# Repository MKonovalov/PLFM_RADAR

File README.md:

# AERIS-10: Open Source Pulse Linear Frequency Modulated Phased Array Radar

AERIS-10 is an open-source, low-cost 10.5 GHz phased array radar system featuring Pulse Linear Frequency Modulated (LFM) modulation. Available in two versions (3km and 20km range, see [Basis of the published performance numbers](#-basis-of-the-published-performance-numbers) for the detection assumptions behind the range figures), it's designed for researchers, drone developers, and serious SDR enthusiasts who want to explore and experiment with phased array radar technology.

## 📡 Overview

The AERIS-10 project aims to democratize radar technology by providing a fully open-source, modular, and hackable radar system. Whether you're a university researcher, a drone startup, or an advanced maker, AERIS-10 offers a platform for experimenting with beamforming, pulse compression, Doppler processing, and target tracking.

## 🔬 Key Features

- **Open Source Hardware & Software** - Complete schematics, PCB layouts, firmware, and software available
- **Dual Version Availability**:
  - **AERIS-10N (Nexus)**: 3km range with 8x16 patch antenna array
  - **AERIS-10E (Extended)**: 20km range with 32x16 dielectric-filled slotted waveguide array
- **Full Electronic Beam Steering** - ±45° electronic steering in elevation and azimuth (characterised for the 8x16 patch array in `docs/AERIS_Antenna_Report.pdf`; the 32x16 waveguide array has no published element-pattern analysis yet — see the basis section below)
- **Advanced Signal Processing** - On-board FPGA handles pulse compression, Doppler FFT, MTI, and CFAR
- **Python GUI** - User-friendly interface with map integration
- **GPS/IMU Integration** - Real-time position and attitude correction
- **Modular Design** - Separate power management, frequency synthesis, and RF boards

## 🏗️ System Architecture

### Hardware Components

The AERIS-10 main sub-systems are:

- **Power Management Board** - Supplies all necessary voltage levels to the electronics components with proper filtering and sequencing (sequencing ensured by the microcontroller)

- **Frequency Synthesizer Board** - Uses a high-performance Low Jitter Clock Generator (AD9523-1) that supplies phase-aligned clock references for:
  - RX and TX Frequency Synthesizers (ADF4382)
  - DAC
  - ADC
  - FPGA

- **Main Board** containing:
  - **DAC** - Generates the RADAR Chirps
  - **2x Microwave Mixers (LTC5552)** - For up-conversion and IF-down-conversion
  - **4x 4-Channel Phase Shifters (ADAR1000)** - For RX and TX chain beamforming
  - **16x Front End Chips (ADTR1107)** - Used for both Low Noise Amplifying (RX) and Power Amplifying (TX) stages
  - **XC7A50T FPGA** - Handles RADAR Signal Processing on the upstream FTG256 board:
    - PLFM Chirps generation via the DAC
    - Raw ADC data read
    - Hybrid Automatic Gain Control (AGC) — cross-layer FPGA/STM32/GUI loop
    - I/Q Baseband Down-Conversion
    - Decimation
    - Filtering
    - Forward FFT
    - Pulse Compression
    - Doppler, MTI and CFAR processing
    - USB Interface
  - **STM32F746xx Microcontroller** - Used for:
    - Power-up and power-down sequencing (see Power Management Excel File)
    - FPGA communication
    - Setup and Interface with:
      - Clock Generator (AD9523-1)
      - 2x Frequency Synthesizers (ADF4382)
      - 4x 4-Channel Phase Shifters (ADAR1000) for RADAR pulse sequencing
      - 2x ADS7830 8-channel I²C ADCs (Main Board, U88 @ 0x48 / U89 @ 0x4A) for 16x Idq measurement, one per PA channel, each sensed through a 5 mΩ shunt on the PA board and an INA241A3 current-sense amplifier (x50) on the Main Board
      - 2x DAC5578 8-channel I²C DACs (Main Board, U7 @ 0x48 / U69 @ 0x49) for 16x Vg control, one per PA channel; closed-loop calibrated at boot to the target Idq
      - GPS module (UM982) for GUI map centering and per-detection position tagging
      - GY-85 IMU for pitch/roll correction of target coordinates
      - BMP180 Barometer
      - Stepper Motor
      - 1x ADS7830 8-channel I²C ADC (Main Board, U10) reading 8 thermistors for thermal monitoring; a single GPIO (EN_DIS_COOLING) switches the cooling fans on when any channel exceeds the threshold
      - RF switches

- **16x Power Amplifier Boards** - Used only for AERIS-10E version, featuring 10Watt QPA2962 GaN amplifier for extended range

- **Antenna Arrays**:
  - **AERIS-10N (Nexus)** - 8x16 patch antenna array
  - **AERIS-10X (Extended)** - 32x16 dielectric-filled slotted waveguide antenna array

- **Miscellaneous Components**:
  - Slip-Ring
  - Stepper Motor and drivers
  - Cooling Fans
  - Enclosure

### Processing Pipeline

1. **Waveform Generation** - DAC creates LFM chirps
2. **Up/Down Conversion** - LTC5552 mixers handle frequency translation
3. **Beam Steering** - ADAR1000 phase shifters control 16 elements
4. **Signal Processing (FPGA)**:
   - Raw ADC data capture
   - I/Q baseband down-conversion
   - Decimation & filtering (CIC/FIR)
   - Pulse compression
   - Doppler FFT processing
   - MTI & CFAR detection
5. **System Management (STM32)**:
   - Power sequencing
   - Peripheral configuration
   - GPS/IMU integration
   - Stepper motor control
6. **Visualization (Python GUI)**:
   - Real-time target plotting
   - Map integration
   - Radar control interface

<!-- V6 GIF removed — V6 is deprecated. V65 Tk and V7 PyQt6 are the active GUIs. -->

## 📊 Technical Specifications

| Parameter | AERIS-10N (Nexus) | AERIS-10X (Extended) |
|-----------|-------------------|----------------------|
| **Frequency** | 10.5 GHz | 10.5 GHz |
| **Max Range** | 3 km ¹ | 20 km ¹ |
| **Antenna** | 8x16 Patch Array | 32x16 Slotted Waveguide |
| **Beam Steering** | Electronic (±45°) ² | Electronic (±45°) ² |
| **Mechanical Scan** | 360° (stepper motor) | 360° (stepper motor) |
| **Output Power** | ~1W×16 | 10W×16 (GaN amplifier) |
| **Processing** | FPGA + STM32 | FPGA + STM32 |
| **Data Interface** | FT2232H USB 2.0 — ~40 MB/s ³ | FT2232H USB 2.0 — ~40 MB/s ³ |

## 📐 Basis of the published performance numbers

The figures above are specifications the design targets, not measured results from a
built unit.  They are only meaningful with their detection assumptions attached, so:

1. **Range.** The 3 km / 20 km figures are single-pulse-budget numbers for a **1 m² RCS**
   target at long dwell (many pulses integrated coherently).  Detection range scales as the
   fourth root of RCS and as the fourth root of integration time, so the same radar sees a
   **0.01 m² target (small drone) at roughly 6 km**, not 20 km.  Quote the target RCS and
   the dwell whenever you quote a range.  The repository carries no link-budget document
   that derives these numbers; `docs/AERIS_Antenna_Report.pdf` covers antenna gain and
   element pattern only.
2. **Beam steering.** ±45° with ~2–3 dB scan loss is the characterised result for the
   **8x16 patch array** (4.72 dBi element, 21.1 dB array factor, ~25.8 dBi realised gain,
   ~75–85° element half-power beamwidth).  Applying the same figure to the 32x16
   slotted-waveguide array is an extrapolation: no element pattern, grating-lobe analysis
   or measured scan loss is published for that array yet.
3. **Data interface.** The FT2232H interface runs at 60 MHz (≈40 MB/s), while the
   400 MSPS ADC produces ≈3.2 Gbit/s raw.  The link therefore carries **processed
   detections/Doppler products only — there is no raw IQ streaming path** at full rate.
4. **The waveguide array's dimensions do not agree inside its own spec.**
   `Dielectric_Filled_Waveguide_Array_Spec.docx` states an inter-column pitch of
   λ₀/2 ≈ 14.28 mm and a **panel height (16 columns) of 223 mm**.  Sixteen columns at
   that pitch span 16 × 14.28 = **228.5 mm**, and the centre-to-centre aperture is
   15 × 14.28 = **214.2 mm** — so 223 mm matches neither convention (5.5 mm and 8.8 mm
   apart respectively).  The spec's own directivity (27.73 dBi) and EIRP (54.8 dBW) are
   derived from A = 0.173 m × 0.223 m = 0.0385 m², i.e. they use the 223 mm height.
   The fabrication drawing has to say which convention it uses before a panel is cut:
   the directivity difference is only ~0.2 dB, so the performance number stands either
   way — it is the drawing that needs reconciling with the spec table.

   **Harmonic emissions.**  Wherever EIRP is quoted above, the harmonic figure belongs with it: the
   PA's 2nd and 3rd harmonics (21.0 and 31.5 GHz) are suppressed by the inline output filter, whose
   specification is in `docs/harmonic-filter.md`.  The chosen part rejects **≥40 dB across
   19.5–32 GHz**, against a requirement of ≥20 dB below carrier at the antenna port — so the design
   carries 20 dB of margin, and the *measured* figure is a first-article item recorded in
   `docs/bring-up-acceptance.md`.

## 🚀 Getting Started

### 🧹 Repository File Placement Policy

To keep the repository root clean and make artifacts easy to find, place generated files in the following locations:

- **Published reports (tracked, GitHub Pages):** `docs/`
  - Example: `docs/AERIS_Simulation_Report_v2.pdf`
- **Simulation-generated outputs (local, gitignored):** `5_Simulations/generated/`
  - Plots, scenario outputs, temporary analysis directories
- **FPGA/Vivado generated artifacts (local, gitignored):** `9_Firmware/9_2_FPGA/reports/`
  - VCD/VVP dumps, temporary CSVs, local report snapshots
- **Reusable FPGA automation scripts (tracked):** `9_Firmware/9_2_FPGA/scripts/`
  - TCL flows, helper scripts used by build/bring-up
- **Generated board artifacts (tracked):** `4_Schematics and Boards Layout/4_7_Production Files/Board_Artifacts/`
  - BOM/CPL CSVs, the DNP list, the inter-board rail map and the accepted-discrepancy baseline,
    all regenerated by `9_Firmware/tools/` and checked in CI

**Do not leave generated artifacts in the repository root.**

### Prerequisites

- Basic understanding of radar principles
- Experience with PCB assembly (for hardware build)
- Python 3.8+ for the GUI software
- FPGA development tools (Vivado) for signal processing modifications

### Hardware Assembly

1. **Order PCBs**: Production outputs are under `/4_Schematics and Boards Layout/4_7_Production Files`
2. **Source Components**: BOM/CPL files are co-located under `/4_Schematics and Boards Layout/4_7_Production Files`
3. **Assembly**: Use the schematics in `/4_Schematics and Boards Layout/4_6_Schematics` together with the production outputs above; a standalone assembly guide is not currently tracked
4. **Antenna**: Choose appropriate array files for your target variant
5. **Enclosure**: Mechanical drawings currently live in `/8_Utils/Mechanical_Drawings`

## 📜 License

This project is open-source but uses **different licenses for hardware and software** to ensure proper legal coverage.

### Hardware Documentation
The hardware design files—including:
- Schematics and PCB layouts (in `/4_Schematics and Boards Layout`)
- Bill of Materials (BOM) files
- Gerber files and manufacturing outputs
- Mechanical drawings and enclosure designs

are licensed under the **CERN Open Hardware Licence Version 2 – Permissive (CERN-OHL-P)** .

This is a hardware-specific license that:
- ✅ Clearly defines "Hardware," "Documentation," and "Products"
- ✅ Includes explicit patent protection for contributors and users
- ✅ Provides stronger liability limitations (important for high-power RF)
- ✅ Aligns with professional open-hardware standards (CERN, OSHWA)

You may use, modify, and sell products based on these designs, provided you:
- Maintain the original copyright notices
- Distribute any modified designs under the same license
- Make your modifications available in Source format

### Software and Firmware
The software components—including:
- FPGA code (VHDL/Verilog in `/9_Firmware`)
- Microcontroller firmware (STM32)
- Python GUI and utilities

remain under the **MIT License** for maximum flexibility.

### Full License Texts
- The complete CERN-OHL-P license text is in the `Licence` file (note the spelling — there is no `LICENSE` file)
- The MIT text covering `9_Firmware` (MCU firmware, FPGA RTL, tools) and the GUI/SDK is in `9_Firmware/LICENSE`

### Why This Change?
Originally, the entire project used the MIT license. The community (special thanks to gmaynez!) pointed out that MIT lacks legal protections needed for physical hardware. The switch to CERN-OHL-P ensures the project is properly protected while maintaining the same permissive spirit.

## 📚 Documentation

Comprehensive documentation is available in the `/docs` folder and served via GitHub Pages at [https://NawfalMotii79.github.io/PLFM_RADAR/docs/](https://NawfalMotii79.github.io/PLFM_RADAR/docs/):

- [System Architecture](/docs/architecture.html)
- [Implementation Log](/docs/implementation-log.html)
- [Hardware Bring-Up Guide](/docs/bring-up.html)
- [Test Reports](/docs/reports.html)
- [Release Notes](/docs/release-notes.html)

### 🔧 Regenerating the BOM and CPL

The production BOM/CPL for each board is generated from the Eagle board files rather than
transcribed by hand, so it can be checked instead of trusted:

```bash
python3 9_Firmware/tools/regenerate_bom.py . --check
```

`--check` exits non-zero when a placed part is missing from a committed BOM spreadsheet,
when a sheet lists a designator that is not on the board, or when a placed part has no
orderable value/MPN.  Run it before ordering boards.

## 🤝 Contributing

We welcome contributions! Please see our [Contributing Guidelines](/CONTRIBUTING.md) for details on repo layout, branch workflow, and basic PR checks.

Areas where help is especially appreciated:
- **RF Engineers**: Review designs, optimize antenna performance
- **FPGA Developers**: Optimize signal processing pipeline
- **Software Developers**: Enhance Python GUI and SDK
- **Beta Testers**: University researchers, drone startups, advanced makers

## 📞 Contact & Collaboration

I welcome serious inquiries from researchers, engineers, and potential collaborators. However, due to the high volume of interest in this project, please understand that I cannot guarantee a response to every message.

- **Technical questions or bug reports**: Please [open a GitHub issue](https://github.com/NawfalMotii79/PLFM_RADAR/issues) so the whole community can benefit from the discussion.
- **Collaboration, licensing, or business inquiries**: 📧 nawfal.motii.33 [at] gmail [dot] com

## 💰 Sponsors

---

**Star ⭐ this repository if you're interested in open-source radar technology!**

*Note: This is an active development project. Some features are still in progress. Check the issues page for known limitations and upcoming features.*

## 19,000 stars – Thank you

This project started in a small workshop in Morocco. Today, 19,000 engineers on GitHub have starred it.

I am genuinely humbled.

**What this tells me:**

- Open source radar matters
- Affordable sensing is needed
- Engineers want to build, not just buy

Thank you to everyone who starred, forked, opened issues, submitted PRs, and shared this project.

The work continues.

**Nawfal Motii**
ABAC INDUSTRY
(http://www.abacindustry.com)

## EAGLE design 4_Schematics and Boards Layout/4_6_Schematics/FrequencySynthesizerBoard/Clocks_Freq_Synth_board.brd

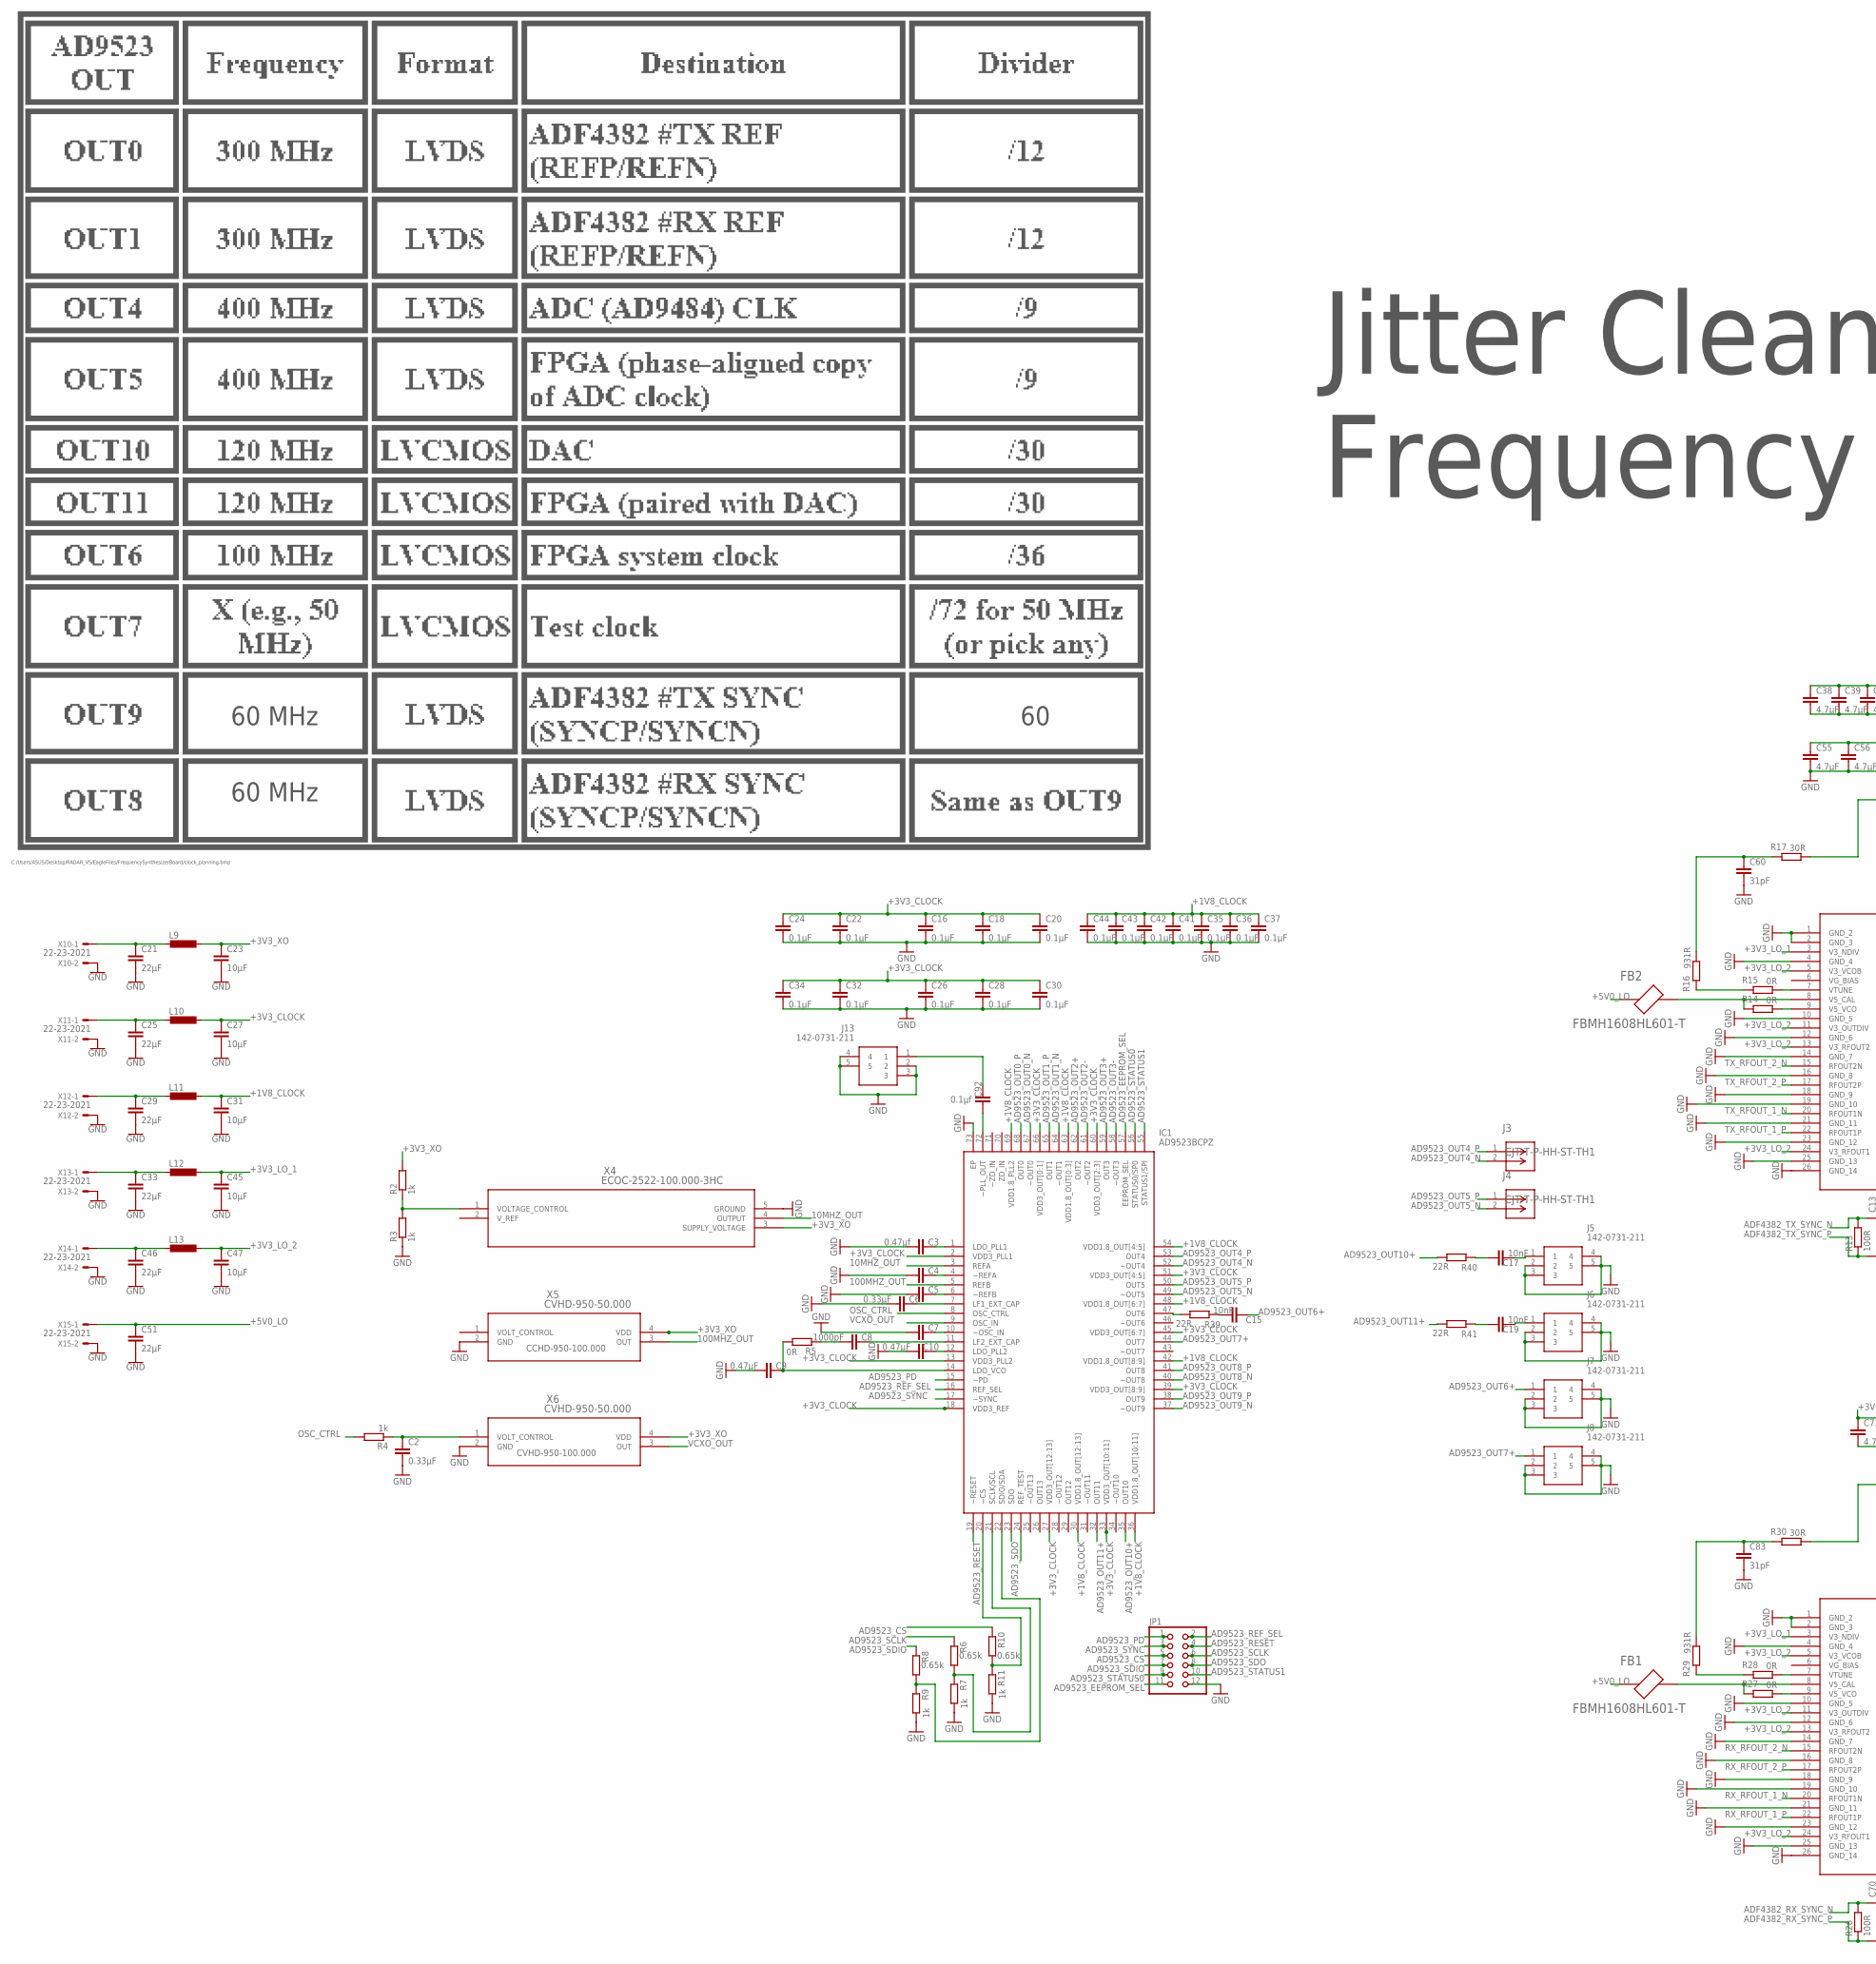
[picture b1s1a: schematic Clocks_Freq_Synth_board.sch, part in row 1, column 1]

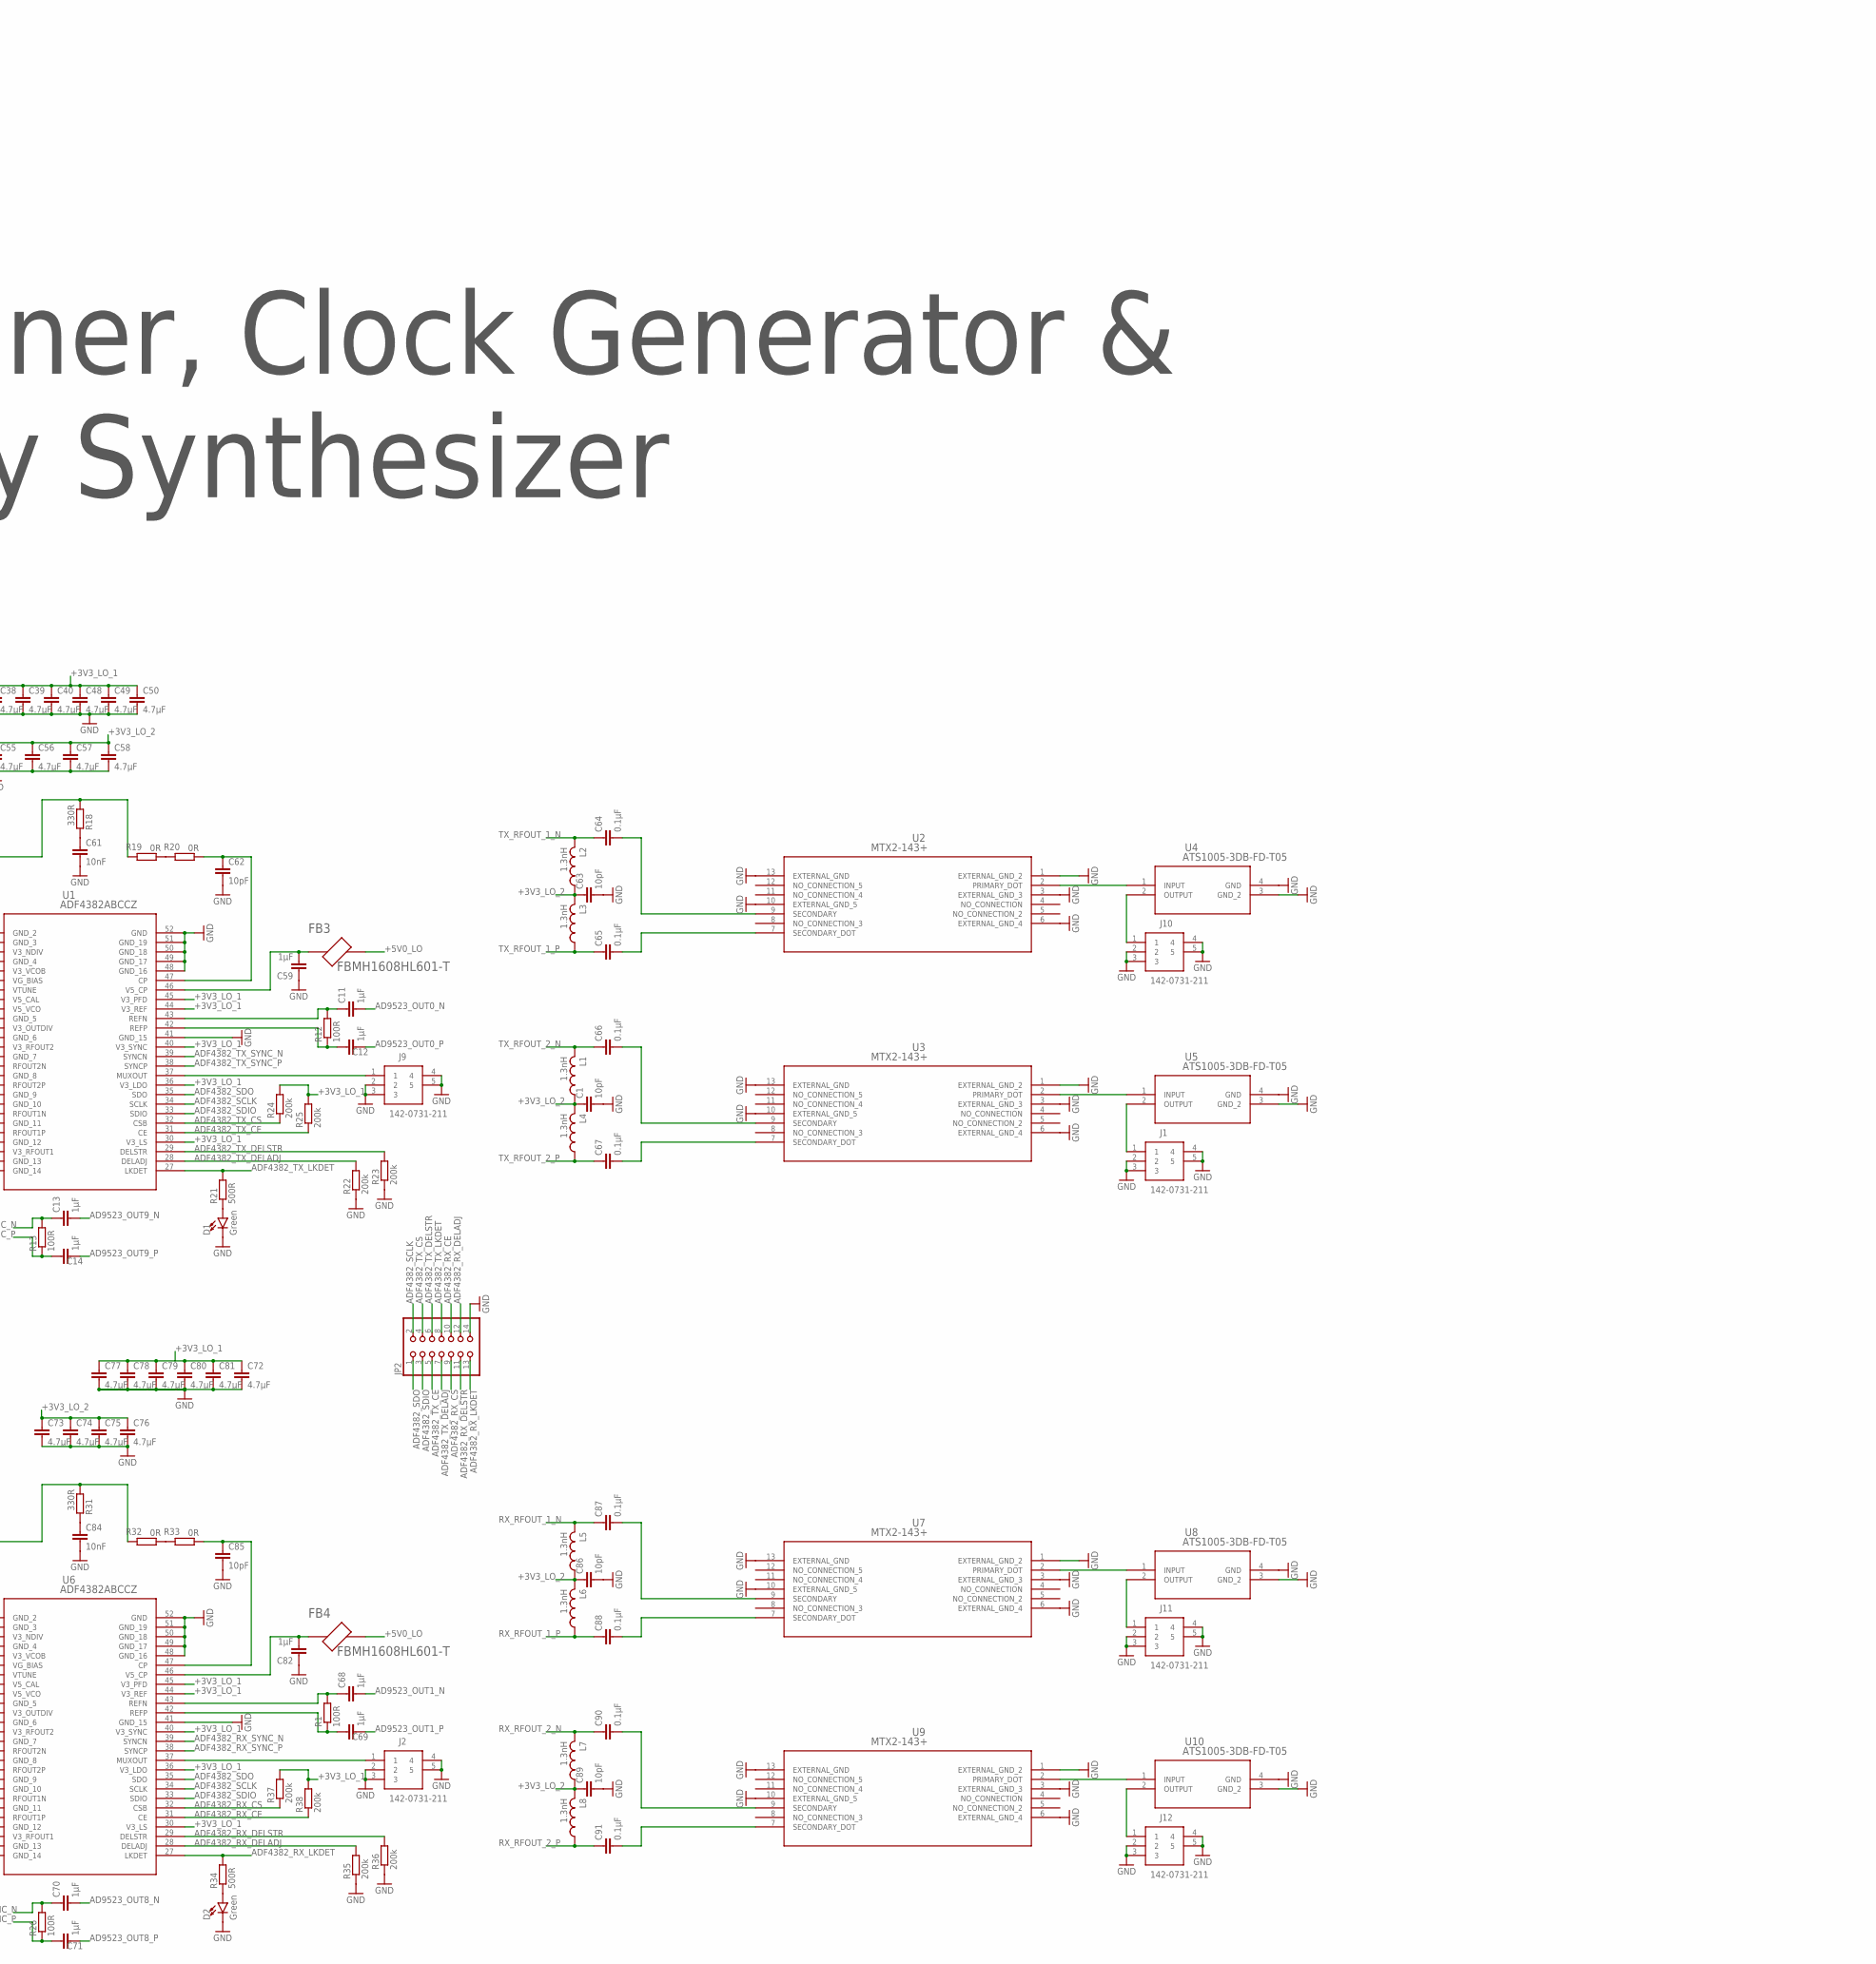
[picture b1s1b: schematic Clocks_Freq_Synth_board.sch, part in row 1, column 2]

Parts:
C1, C62, C63, C85, C86, C89: 10pF; C0201
C2, C6: 0.33µF; C0201
C3: 0.47µf; C0201
C4, C5, C7: C-EUC0201; C0201
C8: 1000pF; C0201
C9, C10: 0.47µF; C0201
C11, C12, C13, C14, C59, C68, C69, C70, C71, C82: 1µF; C0201
C15, C17, C19: 10nF; C0402
C16, C18, C20, C22, C24, C26, C28, C30, C32, C34, C35, C36, C37, C41, C42, C43, C44, C64, C65, C66, C67, C87, C88, C90, C91: 0.1µF; C0201
C21, C25, C29, C33, C46, C51: 22µF; C1210
C23, C27, C31, C45, C47: 10µF; C1210
C38, C39, C40, C48, C49, C50, C55, C56, C57, C58, C72, C73, C74, C75, C76, C77, C78, C79, C80, C81: 4.7µF; C0201
C60, C83: 31pF; C0201
C61, C84: 10nF; C0201
C92: 0.1µf; C0201
D1, D2: Green; LED-0603
FB1, FB2, FB3, FB4: FBMH1608HL601-T; BEADC1608X90N
IC1: AD9523BCPZ; QFN50P1000X1000X100-73N
J1, J2, J5, J6, J7, J8, J9, J10, J11, J12, J13: 142-0731-211; 1420731211
J3, J4: CJT-T-P-HH-ST-TH1; CONN_CJT-T-P-XX-ST-TH1_SAI
JP1: PINHD-2X6; 2X06
JP2: PINHD-2X7; 2X07
L1, L2, L3, L4, L5, L6, L7, L8: 1.3nH; L0201
L9, L10, L11, L12, L13: L-EUL5650M; L5650M
R1, R12, R13, R26: 100R; R0201
R2, R3, R4, R7, R9, R11: 1k; R0201
R5, R14, R15, R19, R20, R27, R28, R32, R33: 0R; R0201
R6, R8, R10: 0.65k; R0201
R16, R29: 931R; R0201
R17, R30: 30R; R0201
R18, R31: 330R; R0201
R21, R34: 500R; R0201
R22, R23, R24, R25, R35, R36, R37, R38: 200k; R0201
R39, R40, R41: 22R; R0201
U1, U6: ADF4382ABCCZ; CC-48-10_ADI
U2, U3, U7, U9: MTX2-143+; DQ1225_MNC
U4, U5, U8, U10: ATS1005-3DB-FD-T05; SMT_DB-FD-T05_SUS
X4: ECOC-2522-100.000-3HC; SMD5_ECOC-2522_25P4X22_ECS
X5, X6: CVHD-950-50.000; SMD4_CVHD-950_CRX
X10, X11, X12, X13, X14, X15: 22-23-2021

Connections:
10MHZ_OUT: IC1.3 (REFA), X4.4 (OUTPUT)
100MHZ_OUT: IC1.5 (REFB), X5.3 (OUT)
+1V8_CLOCK: C31.1, C35.1, C36.1, C37.1, C41.1, C42.1, C43.1, C44.1, IC1.30 (VDD1.8_OUT[12:13]), IC1.36 (VDD1.8_OUT[10:11]), IC1.42 (VDD1.8_OUT[8:9]), IC1.48 (VDD1.8_OUT[6:7]), IC1.54 (VDD1.8_OUT[4:5]), IC1.63 (VDD1.8_OUT[0:3]), IC1.69 (VDD1.8_PLL2), L11.1
+3V3_CLOCK: C16.1, C18.1, C20.1, C22.1, C24.1, C26.1, C27.1, C28.1, C30.1, C32.1, C34.1, IC1.2 (VDD3_PLL1), IC1.13 (VDD3_PLL2), IC1.18 (VDD3_REF), IC1.27 (VDD3_OUT[12:13]), IC1.33 (VDD3_OUT[10:11]), IC1.39 (VDD3_OUT[8:9]), IC1.45 (VDD3_OUT[6:7]), IC1.51 (VDD3_OUT[4:5]), IC1.60 (VDD3_OUT[2:3]), IC1.66 (VDD3_OUT[0:1]), L10.1
+3V3_LO_1: C38.1, C39.1, C40.1, C45.1, C48.1, C49.1, C50.1, C72.1, C77.1, C78.1, C79.1, C80.1, C81.1, L12.1, R24.2, R25.2, R37.2, R38.2, U1.3 (V3_NDIV), U1.30 (V3_LS), U1.36 (V3_LDO), U1.40 (V3_SYNC), U1.44 (V3_REF), U1.45 (V3_PFD), U6.3 (V3_NDIV), U6.30 (V3_LS), U6.36 (V3_LDO), U6.40 (V3_SYNC), U6.44 (V3_REF), U6.45 (V3_PFD)
+3V3_LO_2: C1.1, C47.1, C55.1, C56.1, C57.1, C58.1, C63.1, C73.1, C74.1, C75.1, C76.1, C86.1, C89.1, L1.1, L2.1, L3.2, L4.2, L5.1, L6.2, L7.1, L8.2, L13.1, U1.5 (V3_VCOB), U1.11 (V3_OUTDIV), U1.13 (V3_RFOUT2), U1.24 (V3_RFOUT1), U6.5 (V3_VCOB), U6.11 (V3_OUTDIV), U6.13 (V3_RFOUT2), U6.24 (V3_RFOUT1)
+3V3_XO: C23.1, L9.1, R2.2, X4.3 (SUPPLY_VOLTAGE), X5.4 (VDD), X6.4 (VDD)
+5V0_LO: C51.1, FB1.1, FB2.1, FB3.2, FB4.2, X15.1
AD9523_CS: JP1.5, R10.1
AD9523_EEPROM_SEL: IC1.57 (EEPROM_SEL), JP1.11
AD9523_OUT0_N: C11.2, IC1.67 (~OUT0)
AD9523_OUT0_P: C12.2, IC1.68 (OUT0)
AD9523_OUT1_N: C68.2, IC1.64 (~OUT1)
AD9523_OUT1_P: C69.2, IC1.65 (OUT1)
AD9523_OUT2+: IC1.62 (OUT2)
AD9523_OUT2-: IC1.61 (~OUT2)
AD9523_OUT3+: IC1.59 (OUT3)
AD9523_OUT3-: IC1.58 (~OUT3)
AD9523_OUT4_N: IC1.52 (~OUT4), J3.2
AD9523_OUT4_P: IC1.53 (OUT4), J3.1
AD9523_OUT5_N: IC1.49 (~OUT5), J4.2
AD9523_OUT5_P: IC1.50 (OUT5), J4.1
AD9523_OUT6+: C15.2, J7.1
AD9523_OUT6_DRV: IC1.47 (OUT6), R39.1
AD9523_OUT6_SER: C15.1, R39.2
AD9523_OUT7+: IC1.44 (OUT7), J8.1
AD9523_OUT8_N: C70.2, IC1.40 (~OUT8)
AD9523_OUT8_P: C71.2, IC1.41 (OUT8)
AD9523_OUT9_N: C13.2, IC1.37 (~OUT9)
AD9523_OUT9_P: C14.2, IC1.38 (OUT9)
AD9523_OUT10+: IC1.35 (OUT10), R40.1
AD9523_OUT10_SER: C17.1, R40.2
AD9523_OUT11+: IC1.32 (OUT11), R41.1
AD9523_OUT11_SER: C19.1, R41.2
AD9523_PD: IC1.15 (~PD), JP1.1
AD9523_REF_SEL: IC1.16 (REF_SEL), JP1.2
AD9523_RESET: IC1.19 (~RESET), JP1.4
AD9523_SCLK: JP1.6, R6.1
AD9523_SDIO: JP1.7, R8.1
AD9523_SDO: IC1.23 (SDO), JP1.8
AD9523_STATUS0: IC1.56 (STATUS0/SP0), JP1.9
AD9523_STATUS1: IC1.55 (STATUS1/SPI), JP1.10
AD9523_SYNC: IC1.17 (~SYNC), JP1.3
ADF4382_RX_CE: JP2.10, R38.1, U6.31 (CE)
ADF4382_RX_CS: JP2.9, R37.1, U6.32 (CSB)
ADF4382_RX_DELADJ: JP2.12, R35.2, U6.28 (DELADJ)
ADF4382_RX_DELSTR: JP2.11, R36.2, U6.29 (DELSTR)
ADF4382_RX_LKDET: JP2.13, R34.2, U6.27 (LKDET)
ADF4382_RX_SYNC_N: C70.1, R26.2, U6.39 (SYNCN)
ADF4382_RX_SYNC_P: C71.1, R26.1, U6.38 (SYNCP)
ADF4382_SCLK: JP2.2, U1.34 (SCLK), U6.34 (SCLK)
ADF4382_SDIO: JP2.3, U1.33 (SDIO), U6.33 (SDIO)
ADF4382_SDO: JP2.1, U1.35 (SDO), U6.35 (SDO)
ADF4382_TX_CE: JP2.5, R25.1, U1.31 (CE)
ADF4382_TX_CS: JP2.4, R24.1, U1.32 (CSB)
ADF4382_TX_DELADJ: JP2.7, R22.2, U1.28 (DELADJ)
ADF4382_TX_DELSTR: JP2.6, R23.2, U1.29 (DELSTR)
ADF4382_TX_LKDET: JP2.8, R21.2, U1.27 (LKDET)
ADF4382_TX_SYNC_N: C13.1, R13.2, U1.39 (SYNCN)
ADF4382_TX_SYNC_P: C14.1, R13.1, U1.38 (SYNCP)
GND: C1.2, C2.2, C3.1, C4.1, C5.1, C6.1, C7.1, C9.1, C10.1, C16.2, C18.2, C20.2, C21.2, C22.2, C23.2, C24.2, C25.2, C26.2, C27.2, C28.2, C29.2, C30.2, C31.2, C32.2, C33.2, C34.2, C35.2, C36.2, C37.2, C38.2, C39.2, C40.2, C41.2, C42.2, C43.2, C44.2, C45.2, C46.2, C47.2, C48.2, C49.2, C50.2, C51.2, C55.2, C56.2, C57.2, C58.2, C59.1, C60.2, C61.2, C62.2, C63.2, C72.2, C73.2, C74.2, C75.2, C76.2, C77.2, C78.2, C79.2, C80.2, C81.2, C82.1, C83.2, C84.2, C85.2, C86.2, C89.2, D1.C, D2.C, IC1.73 (EP), J1.2, J1.3, J1.4, J1.5, J2.2, J2.3, J2.4, J2.5, J5.2, J5.3, J5.4, J5.5, J6.2, J6.3, J6.4, J6.5, J7.2, J7.3, J7.4, J7.5, J8.2, J8.3, J8.4, J8.5, J9.2, J9.3, J9.4, J9.5, J10.2, J10.3, J10.4, J10.5, J11.2, J11.3, J11.4, J11.5, J12.2, J12.3, J12.4, J12.5, J13.2, J13.3, J13.4, J13.5, JP1.12, JP2.14, R3.1, R7.2, R9.2, R11.2, R22.1, R23.1, R35.1, R36.1, U1.1 (GND_2), U1.2 (GND_3), U1.4 (GND_4), U1.10 (GND_5), U1.12 (GND_6), U1.14 (GND_7), U1.16 (GND_8), U1.18 (GND_9), U1.19 (GND_10), U1.21 (GND_11), U1.23 (GND_12), U1.25 (GND_13), U1.26 (GND_14), U1.41 (GND_15), U1.48 (GND_16), U1.49 (GND_17), U1.50 (GND_18), U1.51 (GND_19), U1.52 (GND), U2.1 (EXTERNAL_GND_2), U2.3 (EXTERNAL_GND_3), U2.6 (EXTERNAL_GND_4), U2.10 (EXTERNAL_GND_5), U2.13 (EXTERNAL_GND), U3.1 (EXTERNAL_GND_2), U3.3 (EXTERNAL_GND_3), U3.6 (EXTERNAL_GND_4), U3.10 (EXTERNAL_GND_5), U3.13 (EXTERNAL_GND), U4.3 (GND_2), U4.4 (GND), U5.3 (GND_2), U5.4 (GND), U6.1 (GND_2), U6.2 (GND_3), U6.4 (GND_4), U6.10 (GND_5), U6.12 (GND_6), U6.14 (GND_7), U6.16 (GND_8), U6.18 (GND_9), U6.19 (GND_10), U6.21 (GND_11), U6.23 (GND_12), U6.25 (GND_13), U6.26 (GND_14), U6.41 (GND_15), U6.48 (GND_16), U6.49 (GND_17), U6.50 (GND_18), U6.51 (GND_19), U6.52 (GND), U7.1 (EXTERNAL_GND_2), U7.3 (EXTERNAL_GND_3), U7.6 (EXTERNAL_GND_4), U7.10 (EXTERNAL_GND_5), U7.13 (EXTERNAL_GND), U8.3 (GND_2), U8.4 (GND), U9.1 (EXTERNAL_GND_2), U9.3 (EXTERNAL_GND_3), U9.6 (EXTERNAL_GND_4), U9.10 (EXTERNAL_GND_5), U9.13 (EXTERNAL_GND), U10.3 (GND_2), U10.4 (GND), X4.5 (GROUND), X5.2 (GND), X6.2 (GND), X10.2, X11.2, X12.2, X13.2, X14.2, X15.2
unnamed: R2.1, R3.2, X4.1 (VOLTAGE_CONTROL)
unnamed: C2.1, R4.1, X6.1 (VOLT_CONTROL)
unnamed: C3.2, IC1.1 (LDO_PLL1)
unnamed: C6.2, IC1.7 (LF1_EXT_CAP)
unnamed: C4.2, IC1.4 (~REFA)
unnamed: C5.2, IC1.6 (~REFB)
unnamed: C7.2, IC1.10 (~OSC_IN)
unnamed: C8.2, IC1.11 (LF2_EXT_CAP)
unnamed: C8.1, R5.1
unnamed: C9.2, IC1.14 (LDO_VCO), R5.2
unnamed: C10.2, IC1.12 (LDO_PLL2)
unnamed: IC1.21 (SCLK/SCL), R6.2, R7.1
unnamed: IC1.22 (SDIO/SDA), R8.2, R9.1
unnamed: IC1.20 (~CS), R10.2, R11.1
unnamed: C11.1, R12.2, U1.43 (REFN)
unnamed: C12.1, R12.1, U1.42 (REFP)
unnamed: C61.1, R18.2
unnamed: R14.1, U1.9 (V5_VCO)
unnamed: FB2.2, R14.2, U1.8 (V5_CAL)
unnamed: C59.2, FB3.1, U1.46 (V5_CP)
unnamed: R19.1, R20.2
unnamed: R15.1, U1.7 (VTUNE)
unnamed: R15.2, R16.2
unnamed: C60.1, R16.1, R17.2
unnamed: R17.1, R18.1, R19.2
unnamed: C62.1, R20.1, U1.47 (CP)
unnamed: U2.2 (PRIMARY_DOT), U4.1 (INPUT)
unnamed: C65.2, U2.7 (SECONDARY_DOT)
unnamed: J10.1, U4.2 (OUTPUT)
unnamed: C64.2, U2.9 (SECONDARY)
unnamed: C67.2, U3.7 (SECONDARY_DOT)
unnamed: C66.2, U3.9 (SECONDARY)
unnamed: U3.2 (PRIMARY_DOT), U5.1 (INPUT)
unnamed: J1.1, U5.2 (OUTPUT)
unnamed: D1.A, R21.1
unnamed: J9.1, U1.37 (MUXOUT)
unnamed: C68.1, R1.2, U6.43 (REFN)
unnamed: C69.1, R1.1, U6.42 (REFP)
unnamed: R27.1, U6.9 (V5_VCO)
unnamed: FB1.2, R27.2, U6.8 (V5_CAL)
unnamed: C82.2, FB4.1, U6.46 (V5_CP)
unnamed: C84.1, R31.2
unnamed: R32.1, R33.2
unnamed: R28.1, U6.7 (VTUNE)
unnamed: R28.2, R29.2
unnamed: C83.1, R29.1, R30.2
unnamed: R30.1, R31.1, R32.2
unnamed: C85.1, R33.1, U6.47 (CP)
unnamed: D2.A, R34.1
unnamed: J2.1, U6.37 (MUXOUT)
unnamed: C88.2, U7.7 (SECONDARY_DOT)
unnamed: C87.2, U7.9 (SECONDARY)
unnamed: U7.2 (PRIMARY_DOT), U8.1 (INPUT)
unnamed: J11.1, U8.2 (OUTPUT)
unnamed: C91.2, U9.7 (SECONDARY_DOT)
unnamed: C90.2, U9.9 (SECONDARY)
unnamed: U9.2 (PRIMARY_DOT), U10.1 (INPUT)
unnamed: J12.1, U10.2 (OUTPUT)
unnamed: C92.1, IC1.72 (~PLL_OUT)
unnamed: C92.2, J13.1
unnamed: C17.2, J5.1
unnamed: C19.2, J6.1
unnamed: C21.1, L9.2, X10.1
unnamed: C25.1, L10.2, X11.1
unnamed: C29.1, L11.2, X12.1
unnamed: C33.1, L12.2, X13.1
unnamed: C46.1, L13.2, X14.1
OSC_CTRL: IC1.8 (OSC_CTRL), R4.2
RX_RFOUT_1_N: C87.1, L5.2, U6.20 (RFOUT1N)
RX_RFOUT_1_P: C88.1, L6.1, U6.22 (RFOUT1P)
RX_RFOUT_2_N: C90.1, L7.2, U6.15 (RFOUT2N)
RX_RFOUT_2_P: C91.1, L8.1, U6.17 (RFOUT2P)
TX_RFOUT_1_N: C64.1, L2.2, U1.20 (RFOUT1N)
TX_RFOUT_1_P: C65.1, L3.1, U1.22 (RFOUT1P)
TX_RFOUT_2_N: C66.1, L1.2, U1.15 (RFOUT2N)
TX_RFOUT_2_P: C67.1, L4.1, U1.17 (RFOUT2P)
VCXO_OUT: IC1.9 (OSC_IN), X6.3 (OUT)

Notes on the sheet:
CCHD-950-100.000
CVHD-950-100.000
Jitter Cleaner, Clock Generator & Frequency Synthesizer
C:/Users/ASUS/Desktop/RADAR_V5/EagleFiles/FrequencySynthesizerBoard/clock_planning.bmp
60 MHz

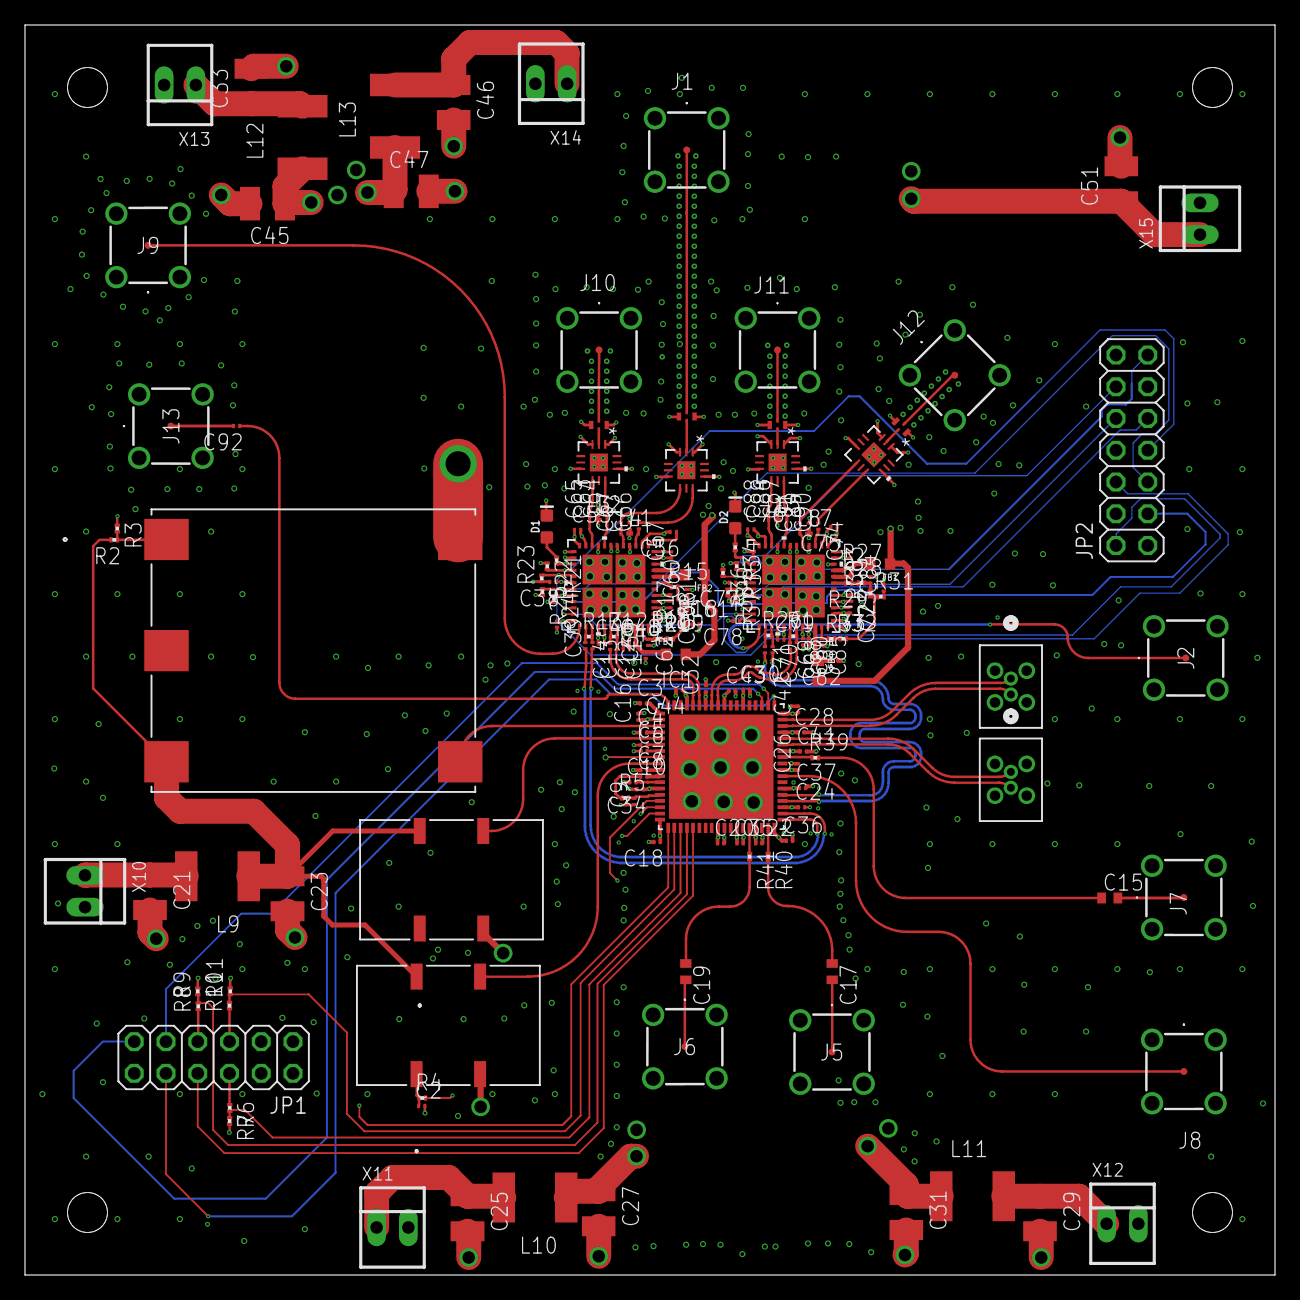
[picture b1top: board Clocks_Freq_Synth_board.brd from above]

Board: 6 copper layers, 100.0 x 100.0 mm, 184 parts (0 on the bottom side), 134 nets.

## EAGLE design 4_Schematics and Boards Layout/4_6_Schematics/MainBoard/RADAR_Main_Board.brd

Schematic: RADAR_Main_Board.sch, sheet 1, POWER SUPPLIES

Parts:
C75, C77, C312, C316, C319, C323, C326, C330, C333, C336, C338, C340: 10µF; C0805
C76, C78, C258, C259, C260, C262, C264, C266, C313, C317, C320, C324, C327, C331, C334, C337, C339, C341, C342, C343, C344, C345, C346, C347, C348, C349, C350, C351: 100nF; C0402
C283, C311, C315, C322, C329: 22µF; C1206
C314, C318, C321, C325, C328, C332, C335: 1nF; C0402
J56, J57, J58, J59: 142-0731-211; 1420731211
L1, L11, L12, L13, L14, L15, L16, L17, L18, L21, L23: L-EUL5650M; L5650M
R174, R175: 0R; R0201
X1, X4, X8, X9, X10, X12, X16, X17, X18, X20, X21, X24, X54, X55, X56: 22-23-2021

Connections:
+1V0_FPGA: X8.1; also elsewhere on the board
+1V8_CLOCK: C311.1, L1.1, X17.1
+1V8_FPGA: X10.1; also elsewhere on the board
+3V3: X24.1; also elsewhere on the board
+3V3_ADAR1_F: C316.1, C317.1, C318.1, L11.2; also elsewhere on the board
+3V3_ADAR2_F: C319.1, C320.1, C321.1, L12.2; also elsewhere on the board
+3V3_ADAR3_F: C323.1, C324.1, C325.1, L13.2; also elsewhere on the board
+3V3_ADAR4_F: C326.1, C327.1, C328.1, L14.2; also elsewhere on the board
+3V3_ADAR12: C315.1, L11.1, L12.1, X20.1
+3V3_ADAR34: C322.1, L13.1, L14.1, X21.1
+3V3_ADTR: X4.1; also elsewhere on the board
+3V3_AN: C283.1, C329.1, L15.1, L16.1, L17.1, L18.1, L21.1, L23.1, X9.1, X56.1; also elsewhere on the board
+3V3_AN1_F: C330.1, C331.1, C332.1, L15.2; also elsewhere on the board
+3V3_AN2_F: C333.1, C334.1, C335.1, L16.2; also elsewhere on the board
+3V3_AN3_F: C75.1, C76.1, C336.1, C337.1, L17.2; also elsewhere on the board
+3V3_AN4_F: C77.1, C78.1, C338.1, C339.1, C340.1, C341.1, L18.2; also elsewhere on the board
+3V3_AN5_F: C258.1, C259.1, C260.1, C262.1, C342.1, C343.1, C344.1, C345.1, L21.2; also elsewhere on the board
+3V3_AN6_F: C264.1, C266.1, C346.1, C347.1, C348.1, C349.1, C350.1, C351.1, L23.2; also elsewhere on the board
+3V3_FPGA: X16.1; also elsewhere on the board
+3V3_VDD_SW: X12.1; also elsewhere on the board
+3V4: X1.1, X54.1; also elsewhere on the board
+5V0_0: X18.1; also elsewhere on the board
+5V5_PA: X55.1; also elsewhere on the board

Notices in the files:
9_Firmware/9_1_Microcontroller/9_1_3_C_Cpp_Code/main.cpp:
Copyright (c) 2025 STMicroelectronics.
All rights reserved.
This software is licensed under terms that can be found in the LICENSE file
README.md:
License: MIT
Hardware: CERN-OHL-P
parts and their libraries:
SparkFun-LED: Licensing: Creative Commons ShareAlike 4.0 International - https://creativecommons.org/licenses/by-sa/4.0
COPYRIGHT: Copyright (C) 2024 Ultra Librarian. All rights reserved.
COPYRIGHT: Copyright (C) 2025 Ultra Librarian. All rights reserved.
